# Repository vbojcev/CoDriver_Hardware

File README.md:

# CoDriver_Hardware
 Electrical Schematics and PCB Design for CoDriver.

 Remember to keep any non-default symbols and footprints inside this repository.

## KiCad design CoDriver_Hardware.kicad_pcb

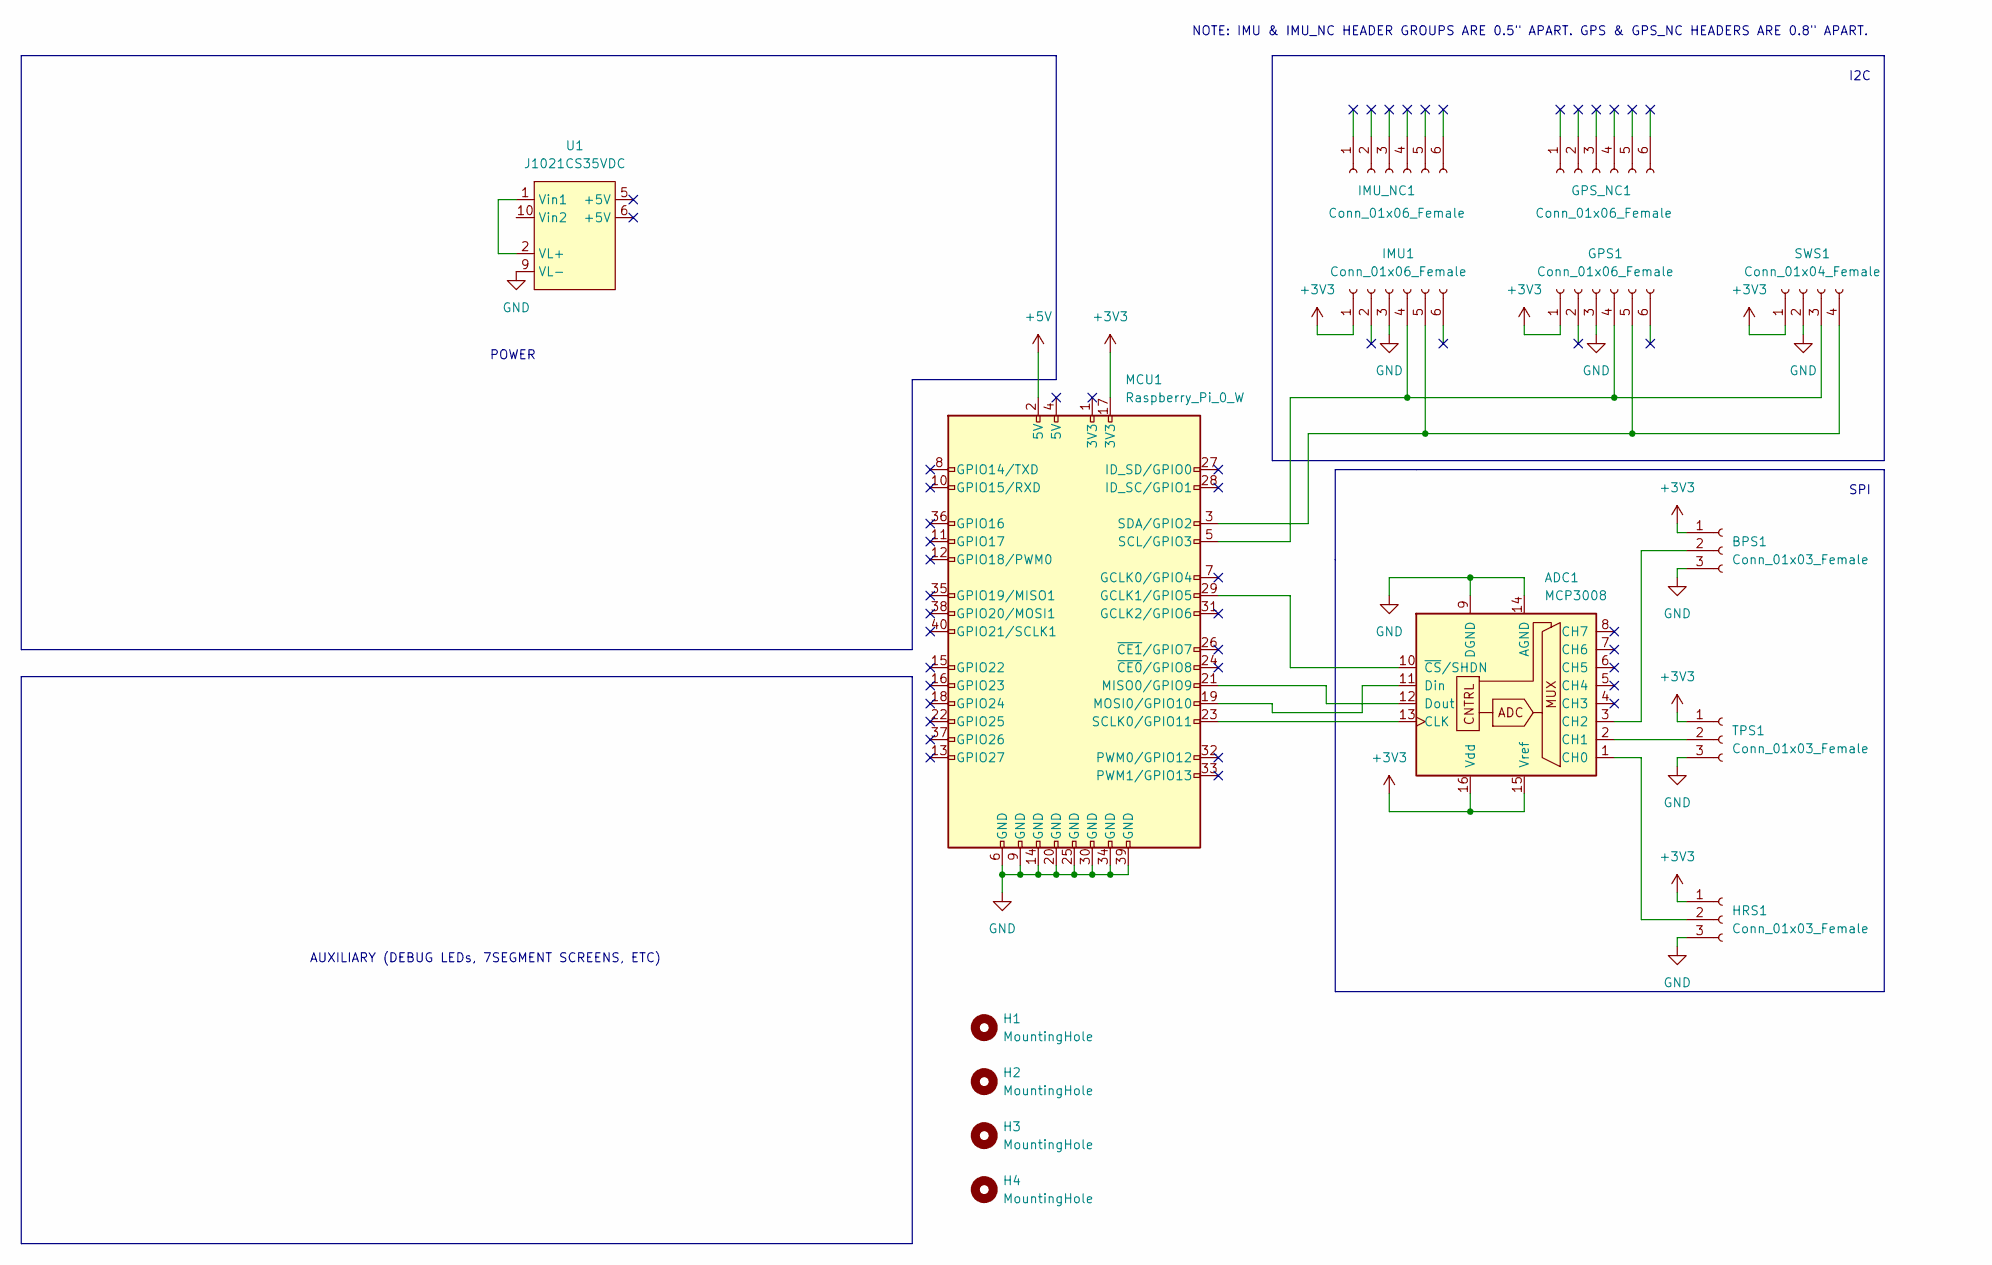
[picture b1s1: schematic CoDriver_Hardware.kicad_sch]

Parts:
ADC1: MCP3008; DIP-16_W7.62mm
BPS1: Conn_01x03_Female; Molex_Micro-Latch_53254-0370_1x03_P2.00mm_Horizontal
GPS1: Conn_01x06_Female; PinSocket_1x06_P2.54mm_Vertical
GPS_NC1: Conn_01x06_Female; PinSocket_1x06_P2.54mm_Vertical
H1, H2, H3, H4: MountingHole; MountingHole_2.7mm_M2.5_Pad
HRS1: Conn_01x03_Female; Molex_Micro-Latch_53254-0370_1x03_P2.00mm_Horizontal
IMU1: Conn_01x06_Female; PinSocket_1x06_P2.54mm_Vertical
IMU_NC1: Conn_01x06_Female; PinSocket_1x06_P2.54mm_Vertical
MCU1: Raspberry_Pi_0_W; PinHeader_2x20_P2.54mm_Vertical
SWS1: Conn_01x04_Female; JST_PH_S4B-PH-K_1x04_P2.00mm_Horizontal
TPS1: Conn_01x03_Female; Molex_Micro-Latch_53254-0370_1x03_P2.00mm_Horizontal
U1: J1021CS35VDC; CoDriverRelay

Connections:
+3V3: ADC1.15 (Vref), ADC1.16 (Vdd), BPS1.1, GPS1.1, HRS1.1, IMU1.1, MCU1.17 (3V3), SWS1.1, TPS1.1
+5V: MCU1.2 (5V)
GND: ADC1.9 (DGND), ADC1.14 (AGND), BPS1.3, GPS1.3, HRS1.3, IMU1.3, MCU1.6 (GND), MCU1.9 (GND), MCU1.14 (GND), MCU1.20 (GND), MCU1.25 (GND), MCU1.30 (GND), MCU1.34 (GND), MCU1.39 (GND), SWS1.2, TPS1.3, U1.9 (VL-)
unnamed: ADC1.1 (CH0), HRS1.2
unnamed: ADC1.2 (CH1), TPS1.2
unnamed: ADC1.3 (CH2), BPS1.2
unnamed: ADC1.10 (~CS/SHDN), MCU1.29 (GCLK1/GPIO5)
unnamed: ADC1.11 (Din), MCU1.19 (MOSI0/GPIO10)
unnamed: ADC1.12 (Dout), MCU1.21 (MISO0/GPIO9)
unnamed: ADC1.13 (CLK), MCU1.23 (SCLK0/GPIO11)
unnamed: GPS1.4, IMU1.4, MCU1.5 (SCL/GPIO3), SWS1.3
unnamed: GPS1.5, IMU1.5, MCU1.3 (SDA/GPIO2), SWS1.4
unnamed: U1.1 (Vin1), U1.2 (VL+)

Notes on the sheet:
SPI
NOTE: IMU & IMU_NC HEADER GROUPS ARE 0.5" APART. GPS & GPS_NC HEADERS ARE 0.8" APART.
I2C
POWER
AUXILIARY (DEBUG LEDs, 7SEGMENT SCREENS, ETC)

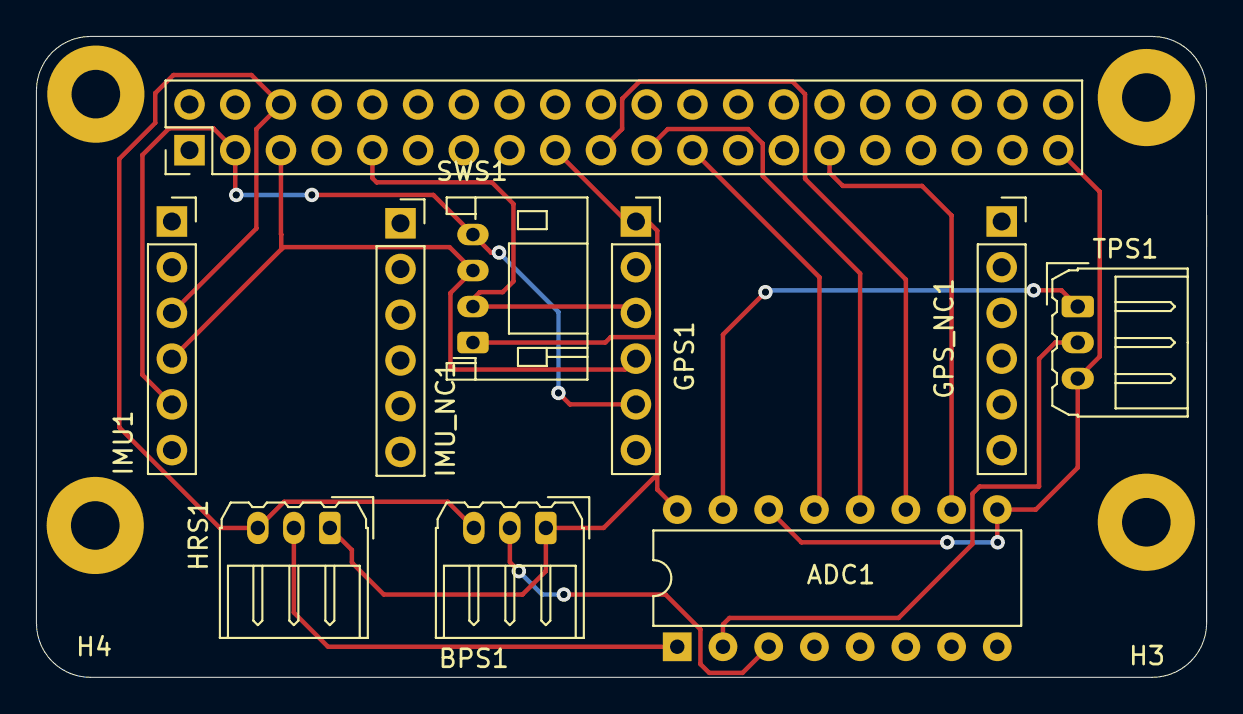
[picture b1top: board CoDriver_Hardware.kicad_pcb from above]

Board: 2 copper layers, 65.0 x 35.6 mm, 14 parts (0 on the bottom side), 11 nets.

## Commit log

2022-06-15 init
2022-07-04 Renaming
2022-07-04 Add Pi Connector
    TODO: GPS + IMU, external connectors (JST 4-pin x 1 and generic 3-pin x 3).
2022-07-05 add BPS, HRS, TPS
2022-07-05 Add essential components
    TODO: Power, secondary connections for IMU/GPS, decoupling capacitors, debug LEDs, PCB
2022-07-05 Add note for physical spacing of headers
2022-07-05 Annotations
2022-07-05 visual enhancements
2022-07-15 PCB Layout
